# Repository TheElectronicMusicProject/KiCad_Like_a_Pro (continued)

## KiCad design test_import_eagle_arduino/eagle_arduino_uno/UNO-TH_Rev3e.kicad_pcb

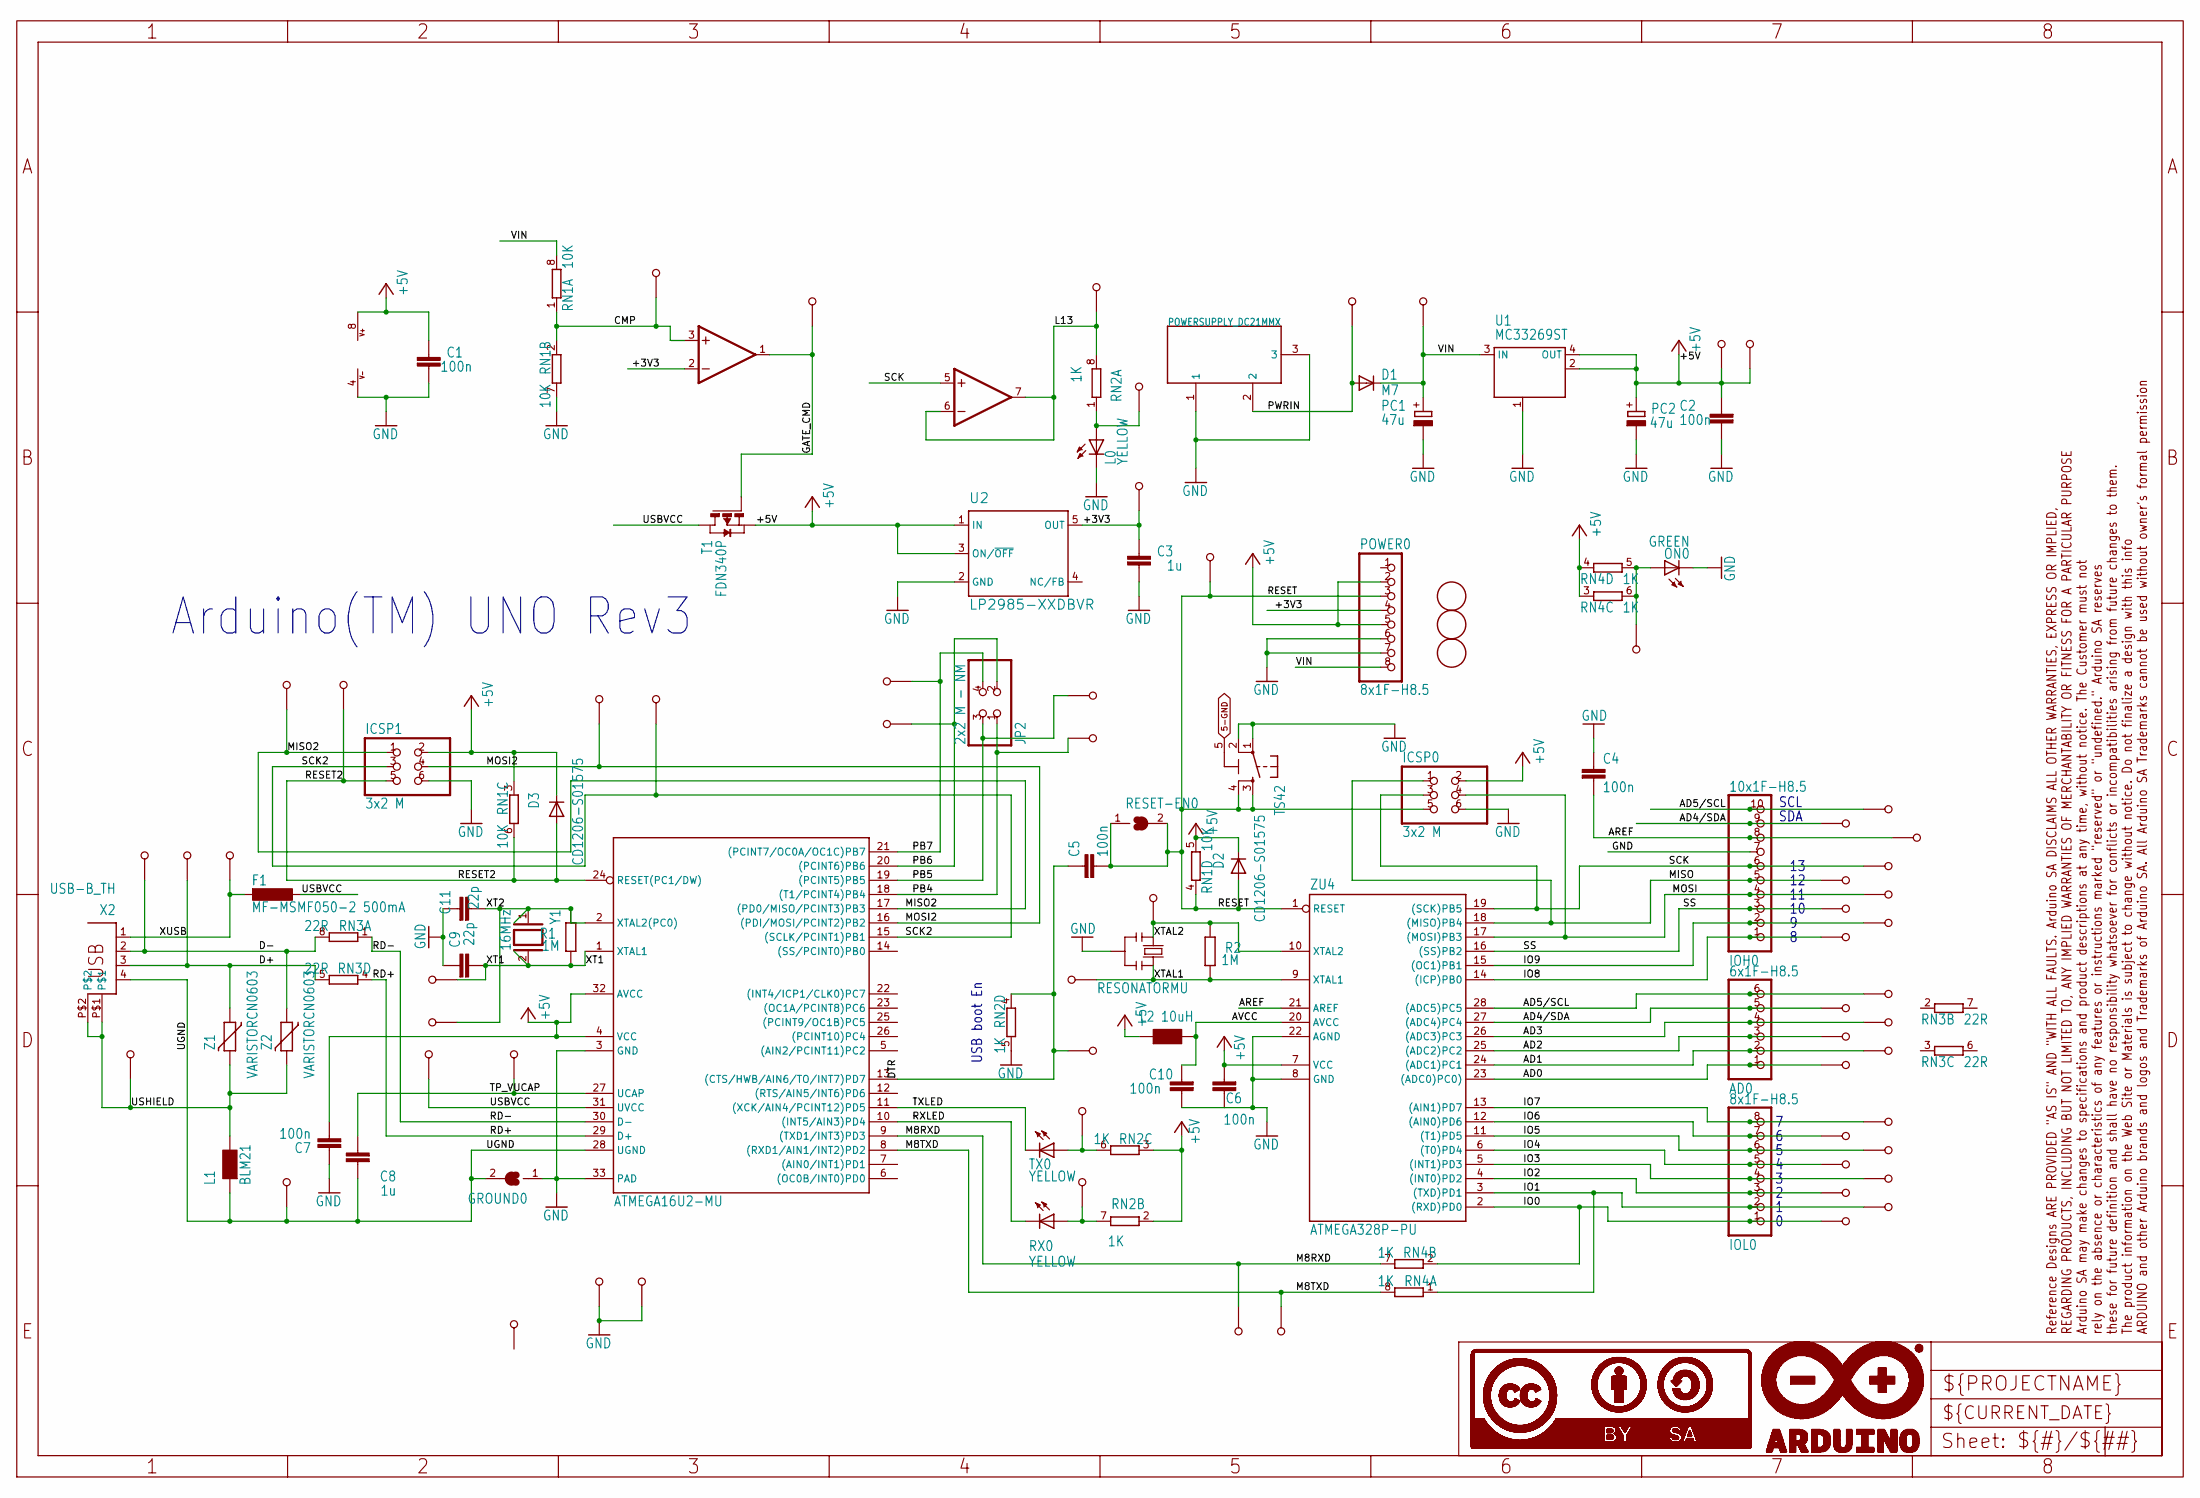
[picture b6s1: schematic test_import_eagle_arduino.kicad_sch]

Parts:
AD0: 6x1F-H8.5; 1X06
C1, C2, C4, C5, C6, C7, C10: 100n; C0603-ROUND
C3, C8: 1u; C0603-ROUND
C9, C11: 22p; C0603-ROUND
D1: M7; SMB
D2, D3: CD1206-S01575; MINIMELF
F1: MF-MSMF050-2 500mA; L1812
FD1, FD2, FD3: FIDUCIALMOUNT; FIDUCIA-MOUNT
FRAME1: A3-FRAME; FRAME
GND_TP0, GND_TP1: TP_SP; TP-SP
GROUND0: SJ
ICSP0, ICSP1: 3x2 M; 2X03
IOH0: 10x1F-H8.5; 1X10
IOL0: 8x1F-H8.5; 1X08
JP2: 2x2 M - NM; 2X02
L0: YELLOW; CHIP-LED0805
L1: BLM21; 0805
L2: 10uH; 0805
ON0: GREEN; CHIP-LED0805
ORIGIN0: TP_SP; TP-SP
PC1, PC2: 47u; PANASONIC_D
POWER0: 8x1F-H8.5; 1X08
R1, R2: 1M; R0603-ROUND
RESET0: TS42
RESET-EN0: SJ
RN1: 10K; CAY16
RN2, RN4: 1K; CAY16
RN3: 22R; CAY16
RX0: YELLOW; CHIP-LED0805
T1: FDN340P; SOT-23
TP_0, TP_1, TP_2, TP_3, TP_3V3, TP_4, TP_5, TP_5V0, TP_5V1, TP_6, TP_7, TP_8, TP_9, TP_10, TP_11, TP_12, TP_13: TP_SP; TP-SP
TP_A0, TP_A1, TP_A2, TP_A3, TP_A4, TP_A5: TP_SP; TP-SP
TP_AREF0: TP_SP; TP-SP
TP_CMP0: TP_SP; TP-SP
TP_D+0: TP_SP; TP-SP
TP_D-0: TP_SP; TP-SP
TP_DTR0: TP_SP; TP-SP
TP_GATE0: TP_SP; TP-SP
TP_LCMD0: TP_SP; TP-SP
TP_LL0: TP_SP; TP-SP
TP_MISO2: TP_SP; TP-SP
TP_MOSI2: TP_SP; TP-SP
TP_ONL0: TP_SP; TP-SP
TP_PB4, TP_PB5, TP_PB6, TP_PB7: TP_SP; TP-SP
TP_PWRIN0: TP_SP; TP-SP
TP_RESET0, TP_RESET2: TP_SP; TP-SP
TP_RX0: TP_SP; TP-SP
TP_RXL0: TP_SP; TP-SP
TP_SCK2: TP_SP; TP-SP
TP_SCL0: TP_SP; TP-SP
TP_SDA0: TP_SP; TP-SP
TP_TX0: TP_SP; TP-SP
TP_TXL0: TP_SP; TP-SP
TP_UGND0: TP_SP; TP-SP
TP_USBVCC0: TP_SP; TP-SP
TP_USH0: TP_SP; TP-SP
TP_VIN0: TP_SP; TP-SP
TP_VUCAP0: TP_SP; TP-SP
TP_XT1, TP_XT2, TP_XT3, TP_XT4: TP_SP; TP-SP
TP_XUSB0: TP_SP; TP-SP
TX0: YELLOW; CHIP-LED0805
U1: MC33269ST; SOT223
U2: LP2985-XXDBVR; SOT23-DBV
U3: ATMEGA16U2-MU; MLF32
U5: LMV358?MM; MSOP08
X1: POWERSUPPLY_DC21MMX; POWERSUPPLY_DC-21MM
X2: USB-B_TH; PN61729
Y1: 16MHz; QS
Y2: RESONATORMU; RESONATOR
Z1, Z2: VARISTORCN0603; CT_CN0603
ZU4: ATMEGA328P-PU; DIL28-3

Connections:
5-GND: RESET0.5 (5-GND)
+3V3: C3.2, POWER0.4, TP_3V3.X, U2.5 (OUT), U5.2 (-IN)
+5V: C1.2, C2.2, C6.2, C7.1, D2.C, D3.C, ICSP0.2, ICSP1.2, L2.1, PC2.+, POWER0.2, POWER0.5, RN1.3 (1), RN1.5 (2), RN2.2 (1), RN2.3 (1), RN4.3 (1), RN4.4 (1), T1.2 (S), TP_5V0.X, TP_5V1.X, U1.2 (OUT@1), U1.4 (OUT), U2.1 (IN), U2.3 (ON/~OFF), U3.4 (VCC), U3.32 (AVCC), U5.8 (V+), ZU4.7 (VCC)
AD0: AD0.1, TP_A0.X, ZU4.23 ((ADC0)PC0))
AD1: AD0.2, TP_A1.X, ZU4.24 ((ADC1)PC1)
AD2: AD0.3, TP_A2.X, ZU4.25 ((ADC2)PC2)
AD3: AD0.4, TP_A3.X, ZU4.26 ((ADC3)PC3)
AD4/SDA: AD0.5, IOH0.9, TP_A4.X, TP_SDA0.X, ZU4.27 ((ADC4)PC4)
AD5/SCL: AD0.6, IOH0.10, TP_A5.X, TP_SCL0.X, ZU4.28 ((ADC5)PC5)
AREF: C4.2, IOH0.8, TP_AREF0.X, ZU4.21 (AREF)
AVCC: C10.2, L2.2, ZU4.20 (AVCC)
CMP: RN1.1, RN1.2 (1), TP_CMP0.X, U5.3 (+IN)
D+: RN3.5 (2), TP_D+0.X, X2.3, Z1.1
D-: RN3.8 (2), TP_D-0.X, X2.2, Z2.1
DTR: C5.1, RN2.4 (1), TP_DTR0.X, U3.13 ((CTS/HWB/AIN6/TO/INT7)PD7)
GATE_CMD: T1.3 (G), TP_GATE0.X, U5.1 (OUT)
GND: C1.1, C2.1, C3.1, C4.1, C6.1, C7.2, C9.2, C10.1, C11.2, GND_TP0.X, GND_TP1.X, GROUND0.1, ICSP0.6, ICSP1.6, IOH0.7, L0.C, ON0.C, PC1.-, PC2.-, POWER0.6, POWER0.7, RESET0.1, RESET0.2, RN1.7 (2), RN2.5 (2), U1.1 (GND/ADJ), U2.2 (GND), U3.3 (GND), U3.33 (PAD), U5.4 (V-), X1.1, X1.3, Y2.2, ZU4.8 (GND), ZU4.22 (AGND)
IO0: IOL0.1, RN4.2 (1), TP_0.X, ZU4.2 ((RXD)PD0)
IO1: IOL0.2, RN4.1, TP_1.X, ZU4.3 ((TXD)PD1)
IO2: IOL0.3, TP_2.X, ZU4.4 ((INT0)PD2)
IO3: IOL0.4, TP_3.X, ZU4.5 ((INT1)PD3)
IO4: IOL0.5, TP_4.X, ZU4.6 ((T0)PD4)
IO5: IOL0.6, TP_5.X, ZU4.11 ((T1)PD5)
IO6: IOL0.7, TP_6.X, ZU4.12 ((AIN0)PD6)
IO7: IOL0.8, TP_7.X, ZU4.13 ((AIN1)PD7)
IO8: IOH0.1, TP_8.X, ZU4.14 ((ICP)PB0)
IO9: IOH0.2, TP_9.X, ZU4.15 ((OC1)PB1)
L13: RN2.8 (2), TP_LCMD0.X, U5.6 (-IN), U5.7 (OUT)
M8RXD: RN4.7 (2), TP_RX0.X, U3.9 ((TXD1/INT3)PD3)
M8TXD: RN4.8 (2), TP_TX0.X, U3.8 ((RXD1/AIN1/INT2)PD2)
MISO: ICSP0.1, IOH0.5, TP_12.X, ZU4.18 ((MISO)PB4)
MISO2: ICSP1.1, TP_MISO2.X, U3.17 ((PD0/MISO/PCINT3)PB3)
MOSI: ICSP0.4, IOH0.4, TP_11.X, ZU4.17 ((MOSI)PB3)
MOSI2: ICSP1.4, TP_MOSI2.X, U3.16 ((PDI/MOSI/PCINT2)PB2)
unnamed: L0.A, RN2.1, TP_LL0.X
unnamed: ON0.A, RN4.5 (2), RN4.6 (2), TP_ONL0.X
unnamed: RN2.7 (2), RX0.A, TP_RXL0.X
unnamed: RN2.6 (2), TP_TXL0.X, TX0.A
PB4: JP2.1, TP_PB4.X, U3.18 ((T1/PCINT4)PB4)
PB5: JP2.3, TP_PB5.X, U3.19 ((PCINT5)PB5)
PB6: JP2.2, TP_PB6.X, U3.20 ((PCINT6)PB6)
PB7: JP2.4, TP_PB7.X, U3.21 ((PCINT7/OC0A/OC1C)PB7)
PWRIN: D1.A, TP_PWRIN0.X, X1.2
RD+: RN3.4 (1), U3.29 (D+)
RD-: RN3.1, U3.30 (D-)
RESET: C5.2, D2.A, ICSP0.5, POWER0.3, RESET0.3, RESET0.4, RESET-EN0.1, RESET-EN0.2, RN1.4 (1), TP_RESET0.X, ZU4.1 (RESET)
RESET2: D3.A, ICSP1.5, RN1.6 (2), TP_RESET2.X, U3.24 (RESET(PC1/DW))
RXLED: RX0.C, U3.10 ((INT5/AIN3)PD4)
SCK: ICSP0.3, IOH0.6, TP_13.X, U5.5 (+IN), ZU4.19 ((SCK)PB5)
SCK2: ICSP1.3, TP_SCK2.X, U3.15 ((SCLK/PCINT1)PB1)
SS: IOH0.3, TP_10.X, ZU4.16 ((SS)PB2)
TP_VUCAP: C8.1, TP_VUCAP0.X, U3.27 (UCAP)
TXLED: TX0.C, U3.11 ((XCK/AIN4/PCINT12)PD5)
UGND: C8.2, GROUND0.2, L1.1, TP_UGND0.X, U3.28 (UGND), X2.4
USBVCC: F1.1, T1.1 (D), TP_USBVCC0.X, U3.31 (UVCC)
USHIELD: L1.2, TP_USH0.X, X2.P$1, X2.P$2, Z1.2, Z2.2
VIN: D1.C, PC1.+, POWER0.8, RN1.8 (2), TP_VIN0.X, U1.3 (IN)
XT1: C9.1, R1.1, TP_XT3.X, U3.1 (XTAL1), Y1.2
XT2: C11.1, R1.2, TP_XT4.X, U3.2 (XTAL2(PC0)), Y1.1
XTAL1: R2.1, TP_XT1.X, Y2.3, ZU4.9 (XTAL1)
XTAL2: R2.2, TP_XT2.X, Y2.1, ZU4.10 (XTAL2)
XUSB: F1.2, TP_XUSB0.X, X2.1

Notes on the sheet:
SDA
SCL
Arduino(TM) UNO Rev3
USB boot En

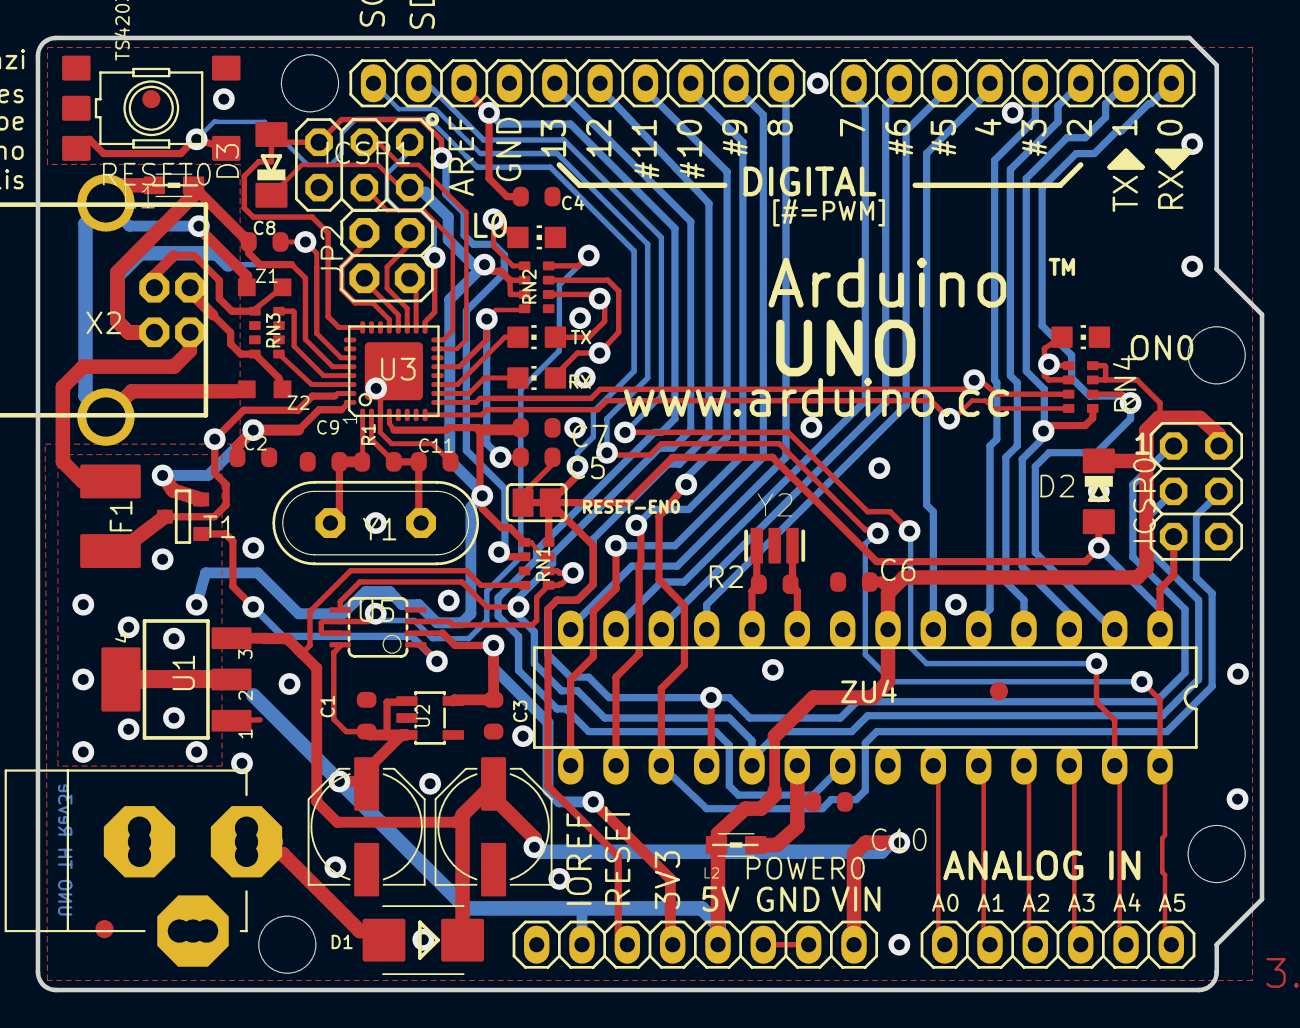
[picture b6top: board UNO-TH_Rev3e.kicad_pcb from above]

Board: 2 copper layers, 68.6 x 53.3 mm, 120 parts (1 on the bottom side), 61 nets.

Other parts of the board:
@HOLE0, @HOLE1, @HOLE2, @HOLE3: (no value)

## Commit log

2023-06-11 Prima commit
    Creato un progetto iniziale e due esempi di progetto
2023-06-14 Cartelle di librerie custom
    Feat: libreria schematico NE555
    Feat: libreria footprint NE555
2023-06-14 Inserito un modello 3D scaricato da internet
    Feat: aggiunto footprint 3D per NE555
2023-06-14 Rimossi file pdf e zip
    Fix: rimossi file pdf e zip anche se aggiunti a LFS
2023-06-15 Iniziato progetto 2
    Feat: inseriti componenti
    Feat: inserito il valore numerico dei componenti C, R
2023-06-19 Modificato il file gitignore
    Fix: ignorato il file di auto salvataggio
2023-06-19 Schematico progetto 2
    Feat: creato lo schema elettrico completo
2023-06-21 Iniziato PCB progetto 2
    Feat: sistemati i componenti
    Feat: incluse le librerie mancanti per i footprint
2023-06-21 Conclusione design PCB progetto 2
    Feat: create tutte le connessioni tra i componenti
    Feat: aggiustata la silkscreen
    Fix: modificato il posizionamento di alcuni componenti
2023-06-21 Correzione schematico e PCB progetto 2
    Fix: rimosso corto circuito tra pin 2 di J3 e J4
    Feat: aggiornati i settaggi della pagina nel PCB
2023-06-21 Inserite 3D shape mancanti
    Feat: aggiunta impronta 3D del jack di alimentazione
    Feat: aggiunta impronta 3D dello switch
    Feat: aggiunte impronte 3D dei connettori 2 poli
2023-06-21 Ritocchi al progetto 2
    Feat: aggiornato il file .gitignore
    Feat: aggiunte le misure di grandezza del PCB
2023-06-22 Iniziato progetto 3
    Feat: impostato lo schematico
    Feat: aggiunti modelli 3D dei componenti importati
2023-06-24 Correzione schematico progetto 3
    Fix: rimosso simbolo di Arduino Pro Mini perché aveva corrotto lo schema elettrico
2023-06-24 Schema elettrico Arduino Pro Mini
    Feat: creato lo schematico di Arduino Pro Mini
2023-06-24 Preparati i componenti per le connessioni (no Arduino Pro Mini)
    Feat: sistemati i componenti
2023-06-25 Creato footprint Arduino Pro Mini
    Feat: creato footprint, numero dei pad e 3D ancora da aggiustare
2023-06-25 Concluso footprint Arduino Pro Mini
    Fix: corretto schematico aggiungendo un secondo pin GND
    Fix: corretti i numeri dei pin nel footprint
    Feat: aggiunto il modello 3D del footprint
2023-06-25 Correzioni minori pin
    Fix: corretta numerazione schematico
    Fix: corretti pad A4/A5 e A6/A7
2023-06-26 Correzione pin 26
    Fix: sistemato il posizionamento del pin 26 nello schematico
2023-06-26 Creazione schematico
    Feat: create le connessioni tra i componenti dello schema elettrico
2023-06-26 Correzione vari pin
    Fix: corretti ulteriori posizionamenti di altri pin
2023-06-26 Correzioni minori e conclusione schematico progetto 2
    Feat: aggiunti mounting hole
    Feat: creata grafica
    Feat: cambiate alcune diciture
    Feat: create net classes
2023-06-26 Iniziato PCB progetto 3
    Feat: impostato PCB
    Feat: inserita outline grezza
2023-06-27 Concluso posizionamento e bordi PCB progetto 3
    Feat: sistemati i bordi della scheda
    Feat: posizionati i footprint sul PCB
2023-06-27 Spostati alcuni componenti nel retro del PCB
    Feat: spostati U1, R1, R2, J1, S1 nel retro
2023-06-27 Completamento tracce progetto 3
    Feat: create tracce per i segnali
    Feat: create filled zone per Vcc e GND
2023-06-28 Ultimi ritocchi progetto 3 e correzioni
    Feat: aggiunte/aggiustate varie silkscreen
    Feat: aggiunti modelli 3D mancanti
    Fix: corretti nomi dei net nello schematico e nel PCB
2023-06-29 Correzioni minori silkscreen progetto 3
    Fix: corrette silkscreen di S2, S3 e U1
2023-06-30 Creata simulazione circuitale
    Feat: preparata la simulazione per transitorio
    Feat: creato il modello per il diodo LED
2023-07-03 Iniziato progetto 4
    Feat: inseriti i componenti nello schematico
2023-07-03 Nuovo foglio e posizionamento componenti
    Feat: creato sheet "Connectors"
    Feat: posizionati i componenti
2023-07-03 Associazione simboli/footprint
    Feat: associati i simboli dei componenti con i relativi footprint
2023-07-04 Completate le connessioni nello schematico
    Feat: connessi tutti i pin in entrambi i fogli
    Feat: effettuato ERC
2023-07-04 Inseriti commenti nello schema
    Feat: aggiunti commenti nello schema elettrico
2023-07-04 Ri-annotati tutti i componenti
    Fix: cancellate annotazioni e ricreate con ordinamento per posizione Y
2023-07-04 Impostato Pcbnew
    Feat: importati i componenti dallo schematico
2023-07-05 Introdotti i componenti nello schema
    Feat: inseriti i componenti nel PCB e posizionati
2023-07-05 Sistemate le dimensioni del PCB
    Feat: ridotte al minimo le dimensioni del PCB
    Feat: spostati i mounting hole
2023-07-05 Completate le connessioni tra i componenti del PCB
    Feat: connessi i vari componenti del PCB
    Feat: effettuato DRC per verifica correttezza
2023-07-06 Inseriti copper fill
    Feat: aggiunto copper fill per GND e Vcc
    Fix: rimosso warning relativo alla silkscreen di U3
    Fix: rimosso warning relativo a una pista di lunghezza 0
2023-07-06 Completata silkscreen
    Feat: aggiunti testi
    Feat: aggiunti loghi
    Fix: sistemate le sovrapposizioni
2023-07-07 Correzione SCK
    Fix: SCL era nominato SCK (erano in corto), ora sono separati
    Fix: numerati i REF degli elementi grafici su Pcbnew
2023-07-07 Correzione connessioni sul PCB
    Fix: rifatti i collegamenti di SCL e SCK
2023-07-07 Aggiunte informazioni - progetto completato
    Feat: aggiunte informazioni sul PCB
2023-07-07 Aggiunti oggetti 3D
    Feat: aggiunti 3D shape per i componenti mancanti
2023-07-08 Aggiornato .gitignore
    Fix: rimosso il track dei file .lck
2023-07-08 Completate le connessioni tra i componenti del PCB
    Feat: connessi i vari componenti del PCB
    Feat: effettuato DRC per verificare correttezza
2023-07-09 Rimosse tutte le connessioni tra i componenti
    Feat: eliminate tracce e via
2023-07-09 Create connessioni mediante Freerouting
    Feat: creato routing automatico
2023-07-10 Importato un progetto Eagle
    Test: creato progetto di test per provare l'importazione di un progetto di Arduino Uno in Eagle
2023-07-12 Creato progetto template prj1
    Feat: progetto template a partire da prj1
    Docs: aggiunto html con informazioni riguardanti il template
2023-07-12 Iniziato progetto 5
    Feat: inserite informazioni sheet
2023-07-13 Inserimento componenti
    Feat: inseriti i simboli dei componenti
    Feat: annotati i simboli in modo coerente allo schema di ESP32
    Feat: sistemati i posizionamenti
2023-07-13 Associazione footprint
    Feat: associati i footprint ai simboli dello schematico (coerentemente con la BOM)
2023-07-16 Connessioni componenti schematico
    Feat: concluso il wiring dei simboli
    Feat: aggiustati alcuni posizionamenti
    Feat: aggiunto commento con tabella di verità
2023-07-17 Importati i footprint in Pcbnew
    Feat: impostato Pcbnew
    Feat: inserite informazioni nel foglio di lavoro
    Feat: importati i componenti da Eeschema
2023-07-17 Posizionati i footprint
    Feat: creato un primo posizionamento finale per i componenti
2023-07-17 Correzione errori clearance e simboli
    Fix: corretto F.Courtyard di MOD1
    Fix: corretto Edge.Cuts di J1
    Fix: modificato board setup per avere conformi i componenti 0402
2023-07-18 Connessioni footprint e fix
    Feat: create gran parte delle connessioni su Pcbnew
    Fix: sistemato il track width della classe POWER
    Fix: sistemata connessione nello schematico, mancava label DTR su pin 28 di U1
2023-07-18 Rimossi tutti gli errori di connessioni
    Feat: creato copper fill per GND
    Feat: creato copper fill per VDD33
    Feat: creata keepout zone sotto all'antenna
    Fix: corrette connessioni mancanti
2023-07-19 Completamento aggiustamenti silkscreen e connessioni
    Feat: aggiunti loghi in silkscreen
    Fix: sistemati i posizionamenti delle silkscreen
    Fix: corretta silkscreen di Q1 e Q2 (footprint)
    Fix: corretta la traccia GND di U1
2023-07-19 Aggiunti oggetti 3D
    Feat: associato, a ogni footprint, il corrispettivo 3D
2023-07-19 Aggiunte informazioni sul PCB
    Docs: aggiunte board characteristics
2023-07-19 Correzione orientamento Q2
    Fix: corretto l'orientamento di Q2 nello schematico
    Fix: riportata la correzione sul PCB
